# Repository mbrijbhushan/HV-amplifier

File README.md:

# HV-amplifier
High-Voltage amplifier design files (+/- 415V, 10 mA current limit, 400 kHz bandwidth)

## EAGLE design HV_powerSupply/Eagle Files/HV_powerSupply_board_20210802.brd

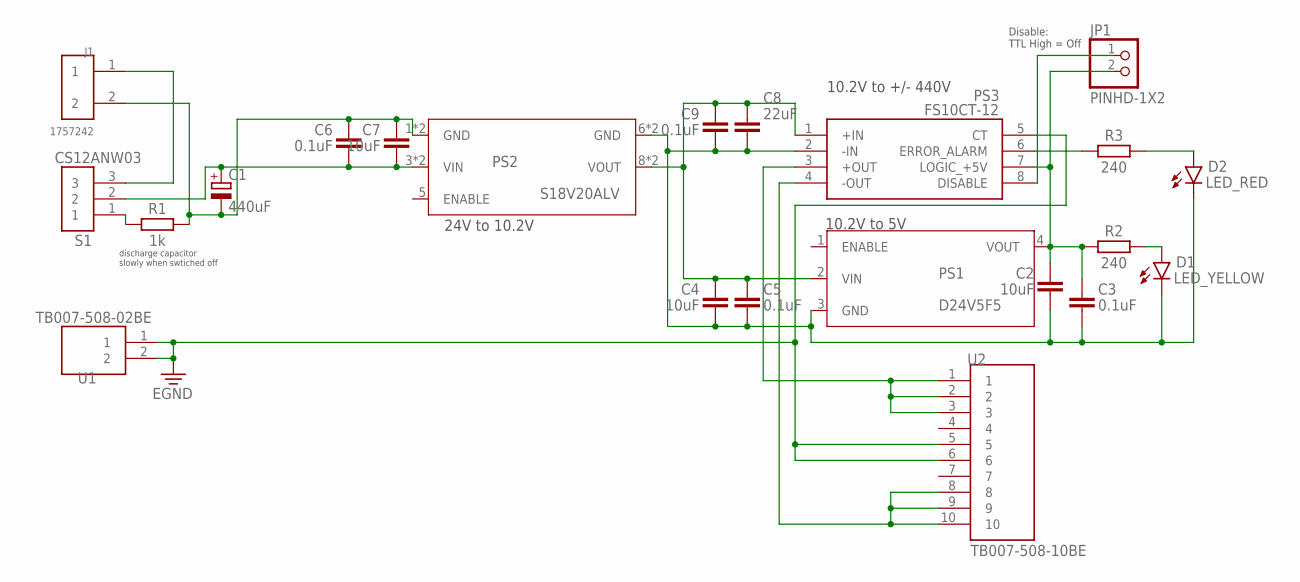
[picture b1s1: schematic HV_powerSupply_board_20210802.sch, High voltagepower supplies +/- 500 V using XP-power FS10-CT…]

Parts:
C1: 440uF; CAPPRD508W65D1000H1100B
C2, C4, C7: 10uF; CAPC3225X135
C3, C5, C6, C9: 0.1uF; CAPC1608X85
C8: 22uF; CAPC3225X135
D1: LED_YELLOW; LEDRD254W60D565H860B_Y
D2: LED_RED; LEDRD254W60D565H860B
J1: 1757242; PHOENIX_1757242
JP1: PINHD-1X2; 1X02
PS1: D24V5F5
PS2: S18V20ALV
PS3: FS10CT-12; FS10CT12
R1: 1k; RESC3216X70
R2, R3: 240; RESC3216X70
S1: CS12ANW03
U1: TB007-508-02BE; CUI_TB007-508-02BE
U2: TB007-508-10BE; CUI_TB007-508-10BE

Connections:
24COM: C2.2, C3.2, C4.2, C5.2, C8.2, C9.2, D1.2 (C), D2.2 (C), PS1.3 (GND), PS2.6 (GND), PS2.7 (GND), PS3.2 (-IN)
24V_COM: C1.2 (-), C6.1, C7.1, J1.2, PS2.1 (GND), PS2.2 (GND), R1.2
+5V: C2.1, C3.1, JP1.2, PS1.4 (VOUT), PS3.7 (LOGIC_+5V), R2.1
ERROR_ALARM: PS3.6 (ERROR_ALARM), R3.1
HV_COM: PS3.5 (CT), U1.1, U1.2, U2.5, U2.6
unnamed: JP1.1, PS3.8 (DISABLE)
unnamed: R1.1, S1.1
unnamed: J1.1, S1.3
unnamed: C4.1, C5.1, C8.1, C9.1, PS1.2 (VIN), PS2.8 (VOUT), PS2.9 (VOUT), PS3.1 (+IN)
unnamed: C1.1 (+), C6.2, C7.2, PS2.3 (VIN), PS2.4 (VIN), S1.2
unnamed: D2.1 (A), R3.2
unnamed: D1.1 (A), R2.2
V+: PS3.3 (+OUT), U2.1, U2.2, U2.3
V-: PS3.4 (-OUT), U2.8, U2.9, U2.10

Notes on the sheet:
24V to 10.2V
10.2V to +/- 440V
10.2V to 5V
discharge capacitor slowly when swtiched off
Disable: TTL High = Off

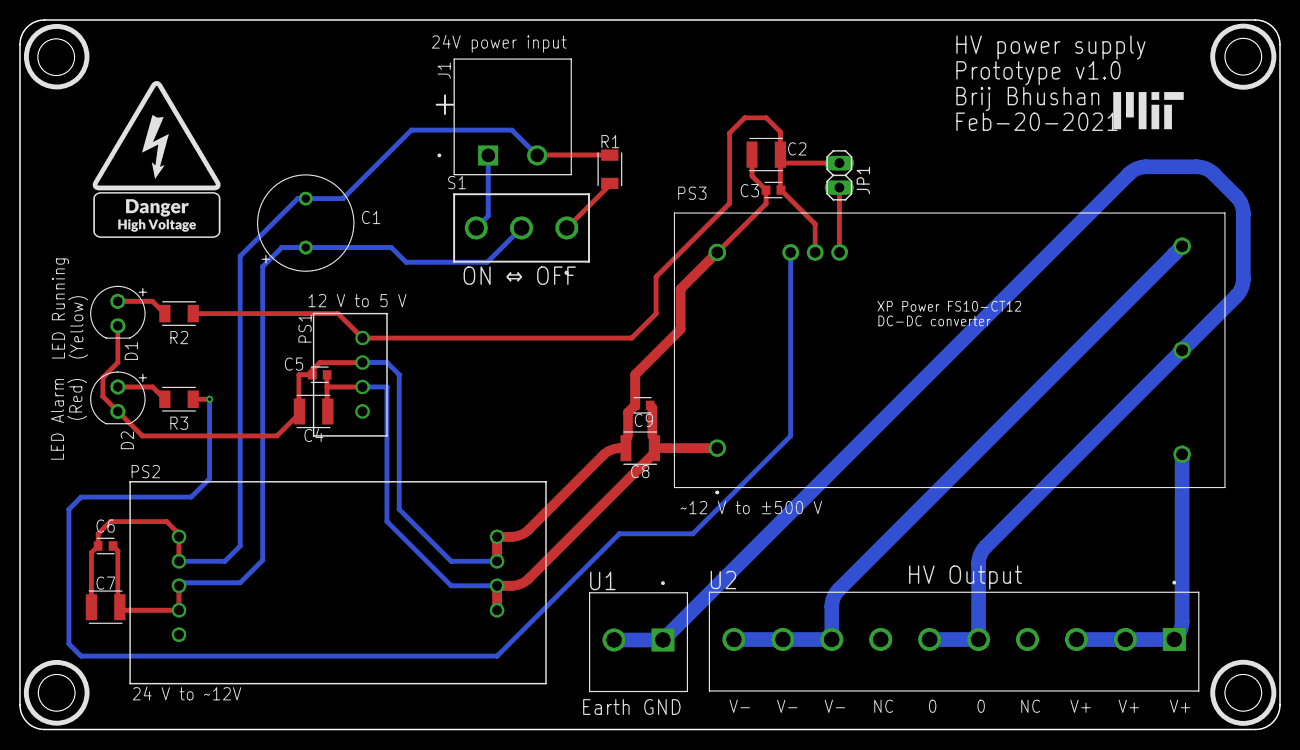
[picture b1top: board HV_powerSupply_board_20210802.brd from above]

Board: 2 copper layers, 130.8 x 73.7 mm, 22 parts (0 on the bottom side), 14 nets.

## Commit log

2021-08-02 CAM files for PCB manufacturing
    HV amplifier and HV power supply
2021-08-02 created subfolders
2021-08-02 added Eagle schematic files
2022-05-28 added mounting design files
